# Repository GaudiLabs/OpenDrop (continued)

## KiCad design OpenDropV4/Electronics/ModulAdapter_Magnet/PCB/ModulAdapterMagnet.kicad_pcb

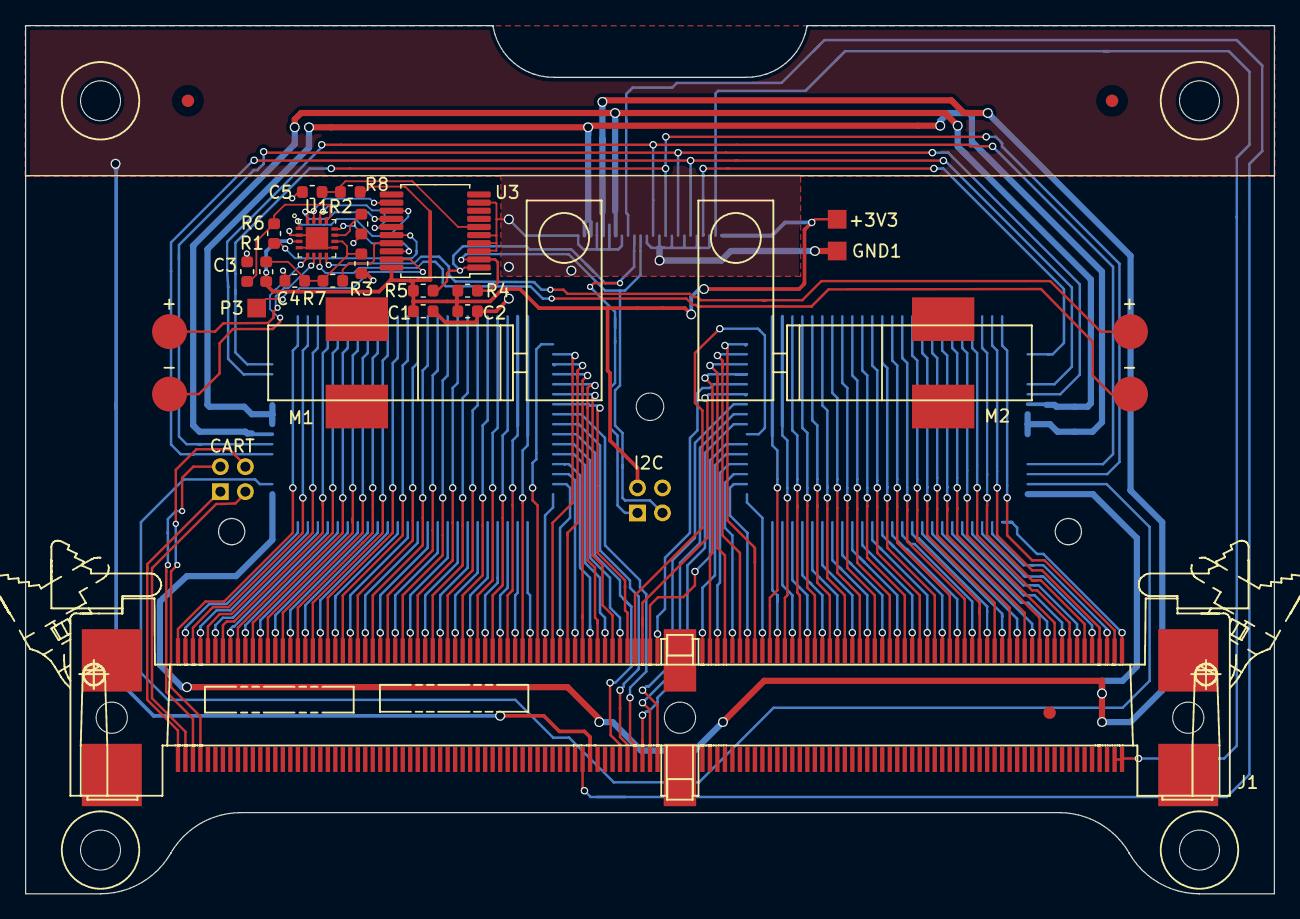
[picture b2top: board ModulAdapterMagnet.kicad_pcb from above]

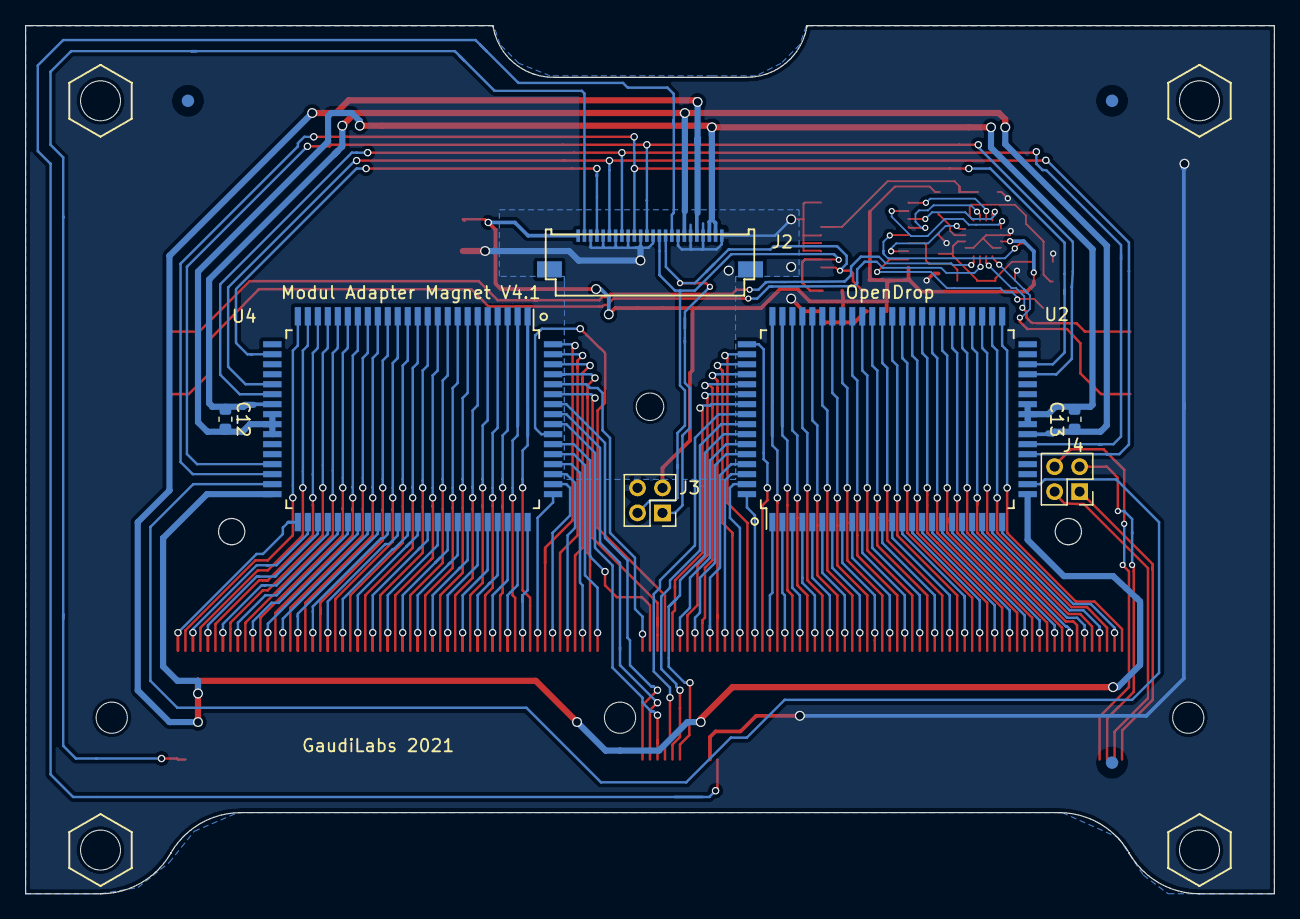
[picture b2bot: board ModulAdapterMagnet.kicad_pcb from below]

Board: 2 copper layers, 100.0 x 69.5 mm, 38 parts (10 on the bottom side), 163 nets.

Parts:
+3V3: ScrewPad2; Measurement_Point_Square-SMD-Pad_Small
C1, C4, C12, C13: 100nF; C_0603_1608Metric
C2: 10uF; C_0603_1608Metric
C3, C5: 22nF; C_0603_1608Metric
GND1: ScrewPad2; Measurement_Point_Square-SMD-Pad_Small
J1: Mini_Dimm_244; MiniDimm_06_244_200
J2: Conn_01x24_Female; FFC_MOLEX_EASYON_05mm_24
J3, J4: Conn_02x02_Top_Bottom; PinHeader_2x02_P2.00mm_Vertical
M1: Motor_DC; GreaMotor6mm_Magnet_l
M2: Motor_DC; GreaMotor6mm_Magnet
P3: ScrewPad2; Measurement_Point_Square-SMD-Pad_Small
P13, P17: ScrewPad1; MountingHoleM3
P14, P15: ScrewPad2; MountingHoleM3
R1: 100k; R_0603_1608Metric
R2: 47k; R_0603_1608Metric
R3, R7: 4.7k; R_0603_1608Metric
R4, R5, R6, R8: 10k; R_0603_1608Metric
U1: TC78H660FTG; P-VQFN16-0303-0.50-001
U2, U4: HV507; PQFP-80_14x20mm_Pitch0.8mm
U3: MCP23008_SS; SSOP-20_5.3x7.2mm_P0.65mm
X1, X2, X3, X4, X5, X6: PAD; Fiducial_1mm_Dia_2.54mm_Outer_CopperBottom

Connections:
+3V3: +3V3.1, C1.1, C2.1, J2.1, J3.3, R1.1, R4.1, R5.1, R8.1, U1.3, U3.20
BL_C: J2.6, U2.29, U4.29
BOOST: R7.2, U3.17
CLK_C: J2.12, U2.37, U4.37
DIG0: J2.15, J3.1, R5.2, U3.1
DIG1: J2.14, J3.2, R4.2, U3.2
DI_C: J2.4, U4.26
ENABLE_A: U1.15, U3.12
ENABLE_B: U1.16, U3.14
GND: C1.2, C2.2, C3.2, C4.2, C5.2, GND1.1, J1.56, J2.3, J2.5, J2.7, J2.9, J2.11, J2.13, J2.17, J2.19, J2.21, J2.24, J3.4, R2.2, R3.2, U1.2, U1.4, U1.9, U1.17, U3.3, U3.4, U3.5, U3.9
GND_C: C12.2, C13.2, J2.22, J2.23, U2.32, U2.33, U2.34, U4.32, U4.33, U4.34
J1: J1.1, J4.1
J2: J1.2, J4.2
J3: J1.3, J4.3
J4: J1.4, J4.4
LE_C: J2.10, U2.38, U4.38
MODE: R6.2, U3.16
unnamed: C3.1, R6.1, U1.13
unnamed: C4.1, R1.2, R3.1, R7.1, U1.10
unnamed: C5.1, R8.2, U3.6
unnamed: J1.60, U2.74
unnamed: J1.61, U2.73
unnamed: J1.62, U2.72
unnamed: J1.63, U4.72
unnamed: J1.64, U4.73
unnamed: J1.65, U4.74
unnamed: J1.123, U2.41
unnamed: J1.124, U2.24
unnamed: J1.125, U2.42
unnamed: J1.126, U2.23
unnamed: J1.127, U2.43
unnamed: J1.128, U2.22
unnamed: J1.129, U2.44
unnamed: J1.130, U2.21
unnamed: J1.131, U2.45
unnamed: J1.132, U2.20
unnamed: J1.133, U2.46
unnamed: J1.134, U2.19
unnamed: J1.135, U2.47
unnamed: J1.136, U2.18
unnamed: J1.137, U2.48
unnamed: J1.138, U2.17
unnamed: J1.139, U2.49
unnamed: J1.140, U2.16
unnamed: J1.141, U2.50
unnamed: J1.142, U2.15
unnamed: J1.143, U2.51
unnamed: J1.144, U2.14
unnamed: J1.145, U2.52
unnamed: J1.146, U2.13
unnamed: J1.147, U2.53
unnamed: J1.148, U2.12
unnamed: J1.149, U2.54
unnamed: J1.150, U2.11
unnamed: J1.151, U2.55
unnamed: J1.152, U2.10
unnamed: J1.153, U2.56
unnamed: J1.154, U2.9
unnamed: J1.155, U2.57
unnamed: J1.156, U2.8
unnamed: J1.157, U2.58
unnamed: J1.158, U2.7
unnamed: J1.159, U2.59
unnamed: J1.160, U2.6
unnamed: J1.161, U2.60
unnamed: J1.162, U2.5
unnamed: J1.163, U2.61
unnamed: J1.164, U2.4
unnamed: J1.165, U2.62
unnamed: J1.166, U2.3
unnamed: J1.167, U2.63
unnamed: J1.168, U2.2
unnamed: J1.169, U2.64
unnamed: J1.170, U2.1
unnamed: J1.171, U2.65
unnamed: J1.172, U2.80
unnamed: J1.173, U2.66
unnamed: J1.174, U2.79
unnamed: J1.175, U2.67
unnamed: J1.176, U2.78
unnamed: J1.177, U2.68
unnamed: J1.178, U2.77
unnamed: J1.179, U2.69
unnamed: J1.180, U2.76
unnamed: J1.181, U2.70
unnamed: J1.182, U2.75
unnamed: J1.183, U2.71
unnamed: J1.184, U4.71
unnamed: J1.185, U4.75
unnamed: J1.186, U4.70
unnamed: J1.187, U4.76
unnamed: J1.188, U4.69
unnamed: J1.189, U4.77
unnamed: J1.190, U4.68
unnamed: J1.191, U4.78
unnamed: J1.192, U4.67
unnamed: J1.193, U4.79
unnamed: J1.194, U4.66
unnamed: J1.195, U4.80
unnamed: J1.196, U4.65
unnamed: J1.197, U4.1
unnamed: J1.198, U4.64
unnamed: J1.199, U4.2
unnamed: J1.200, U4.63
unnamed: J1.201, U4.3
unnamed: J1.202, U4.62
unnamed: J1.203, U4.4
unnamed: J1.204, U4.61
unnamed: J1.205, U4.5
unnamed: J1.206, U4.60
unnamed: J1.207, U4.6
unnamed: J1.208, U4.59
unnamed: J1.209, U4.7
unnamed: J1.210, U4.58
unnamed: J1.211, U4.8
unnamed: J1.212, U4.57
unnamed: J1.213, U4.9
unnamed: J1.214, U4.56
unnamed: J1.215, U4.10
unnamed: J1.216, U4.55
unnamed: J1.217, U4.11
unnamed: J1.218, U4.54
unnamed: J1.219, U4.12
unnamed: J1.220, U4.53
unnamed: J1.221, U4.13
unnamed: J1.222, U4.52
unnamed: J1.223, U4.14
unnamed: J1.224, U4.51
unnamed: J1.225, U4.15
unnamed: J1.226, U4.50
unnamed: J1.227, U4.16
unnamed: J1.228, U4.49
unnamed: J1.229, U4.17
unnamed: J1.230, U4.48
unnamed: J1.231, U4.18
unnamed: J1.232, U4.47
unnamed: J1.233, U4.19
unnamed: J1.234, U4.46
unnamed: J1.235, U4.20
unnamed: J1.236, U4.45
unnamed: J1.237, U4.21
unnamed: J1.238, U4.44
unnamed: J1.239, U4.22
unnamed: J1.240, U4.43
unnamed: J1.241, U4.23
unnamed: J1.242, U4.42
unnamed: J1.243, U4.24
unnamed: J1.244, U4.41
unnamed: M1.1, U1.5
unnamed: M1.2, U1.6
unnamed: M2.1, U1.8
unnamed: M2.2, U1.7
unnamed: P3.1, U3.19
unnamed: R2.1, U1.11
unnamed: U2.26, U4.39
PHASE_A: U1.1, U3.13
PHASE_B: U1.14, U3.15
POL_C: J2.8, U2.30, U4.30
SENS_PAD: J1.55, J2.16
STBY: U1.12, U3.18
VDD_C: C12.1, C13.1, J2.18, U2.31, U4.31
V_GND: J1.121, J1.122, J2.2
V_HV_C: J2.20, U2.25, U4.40

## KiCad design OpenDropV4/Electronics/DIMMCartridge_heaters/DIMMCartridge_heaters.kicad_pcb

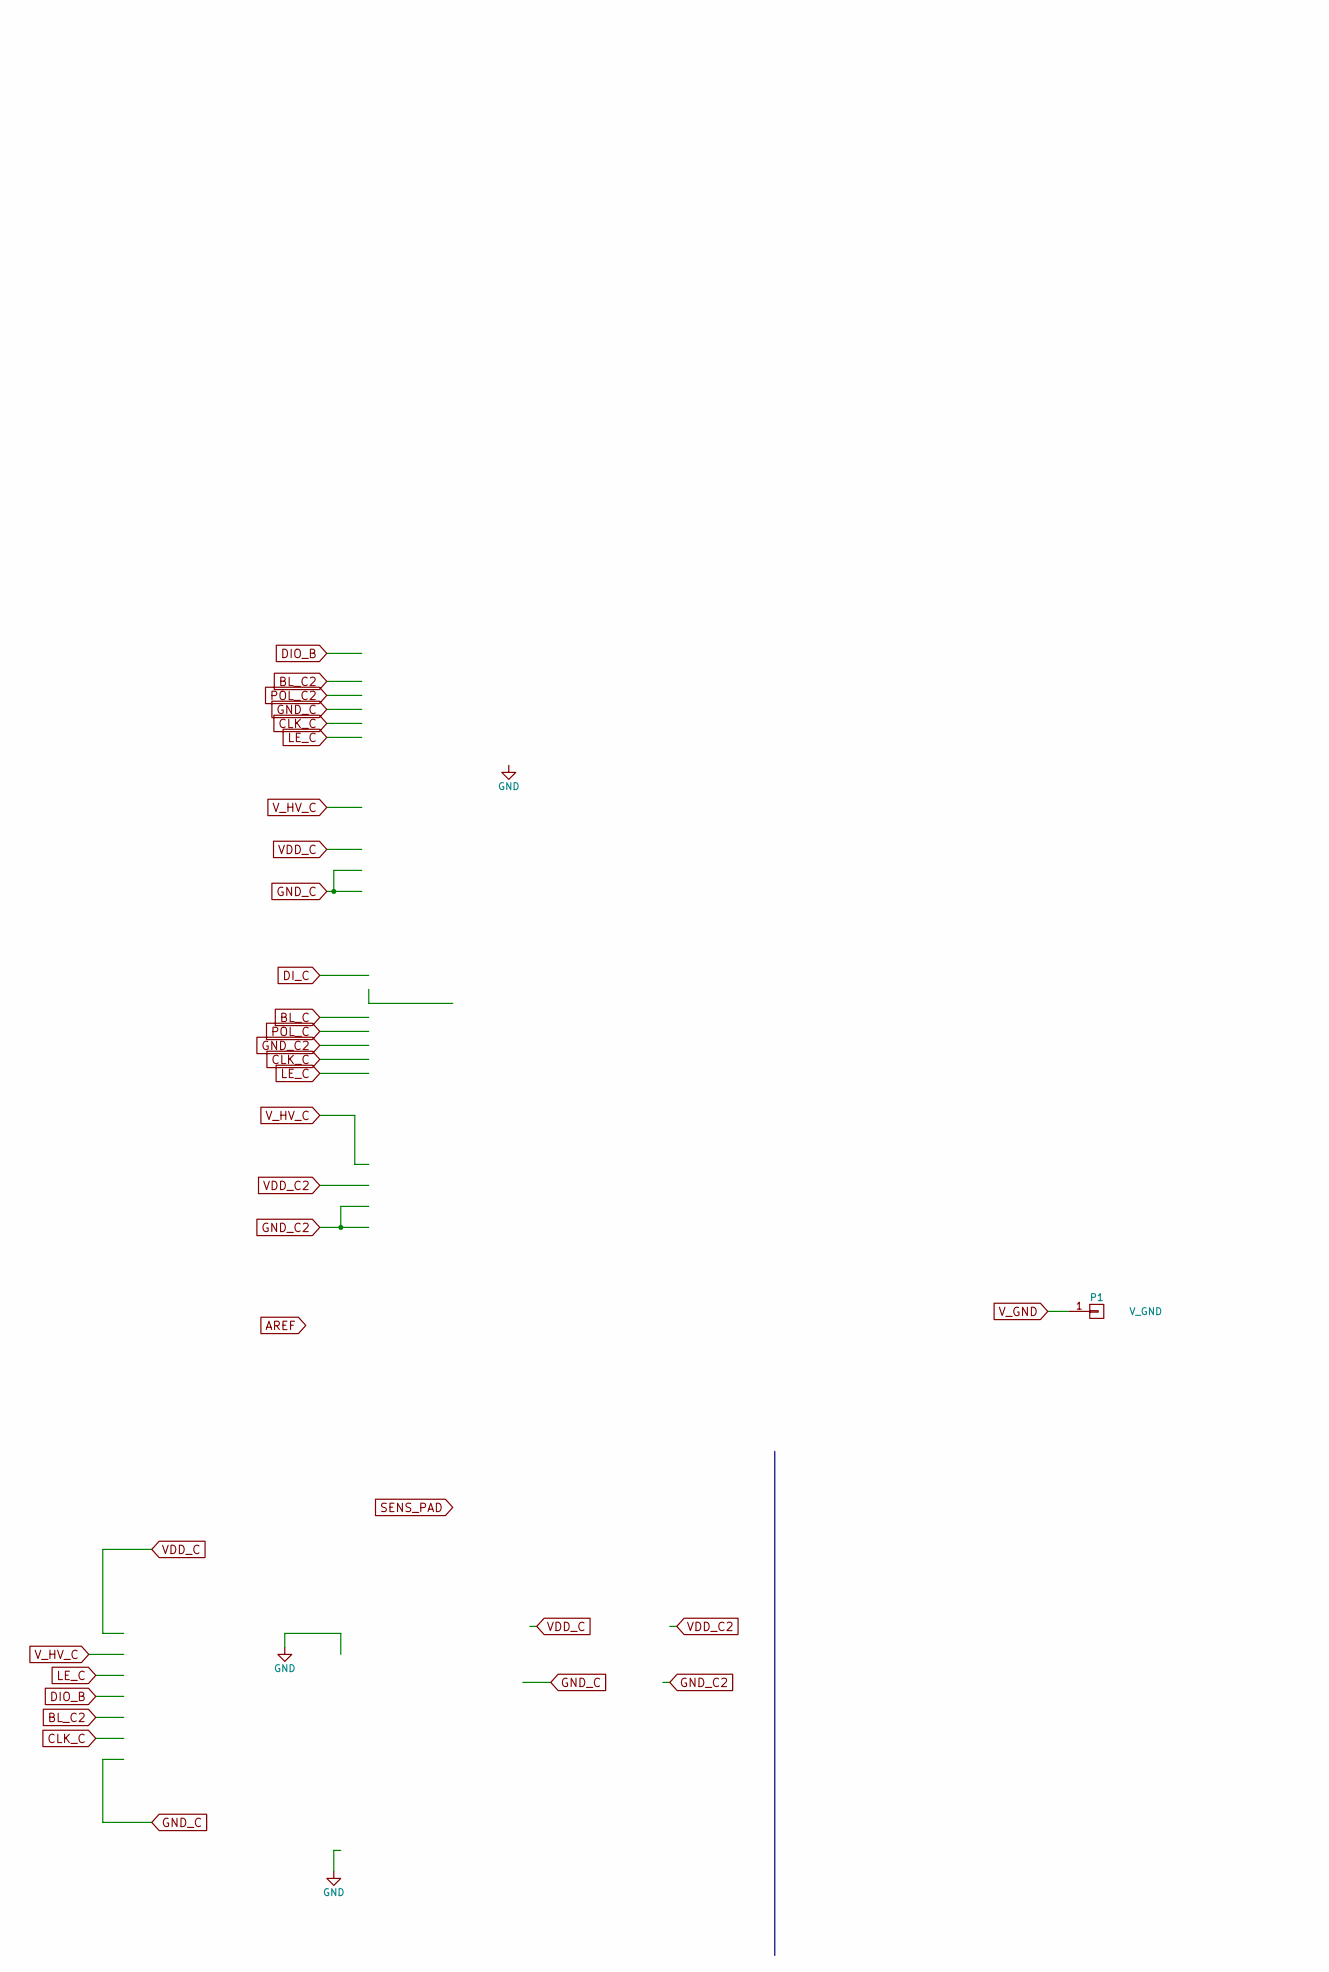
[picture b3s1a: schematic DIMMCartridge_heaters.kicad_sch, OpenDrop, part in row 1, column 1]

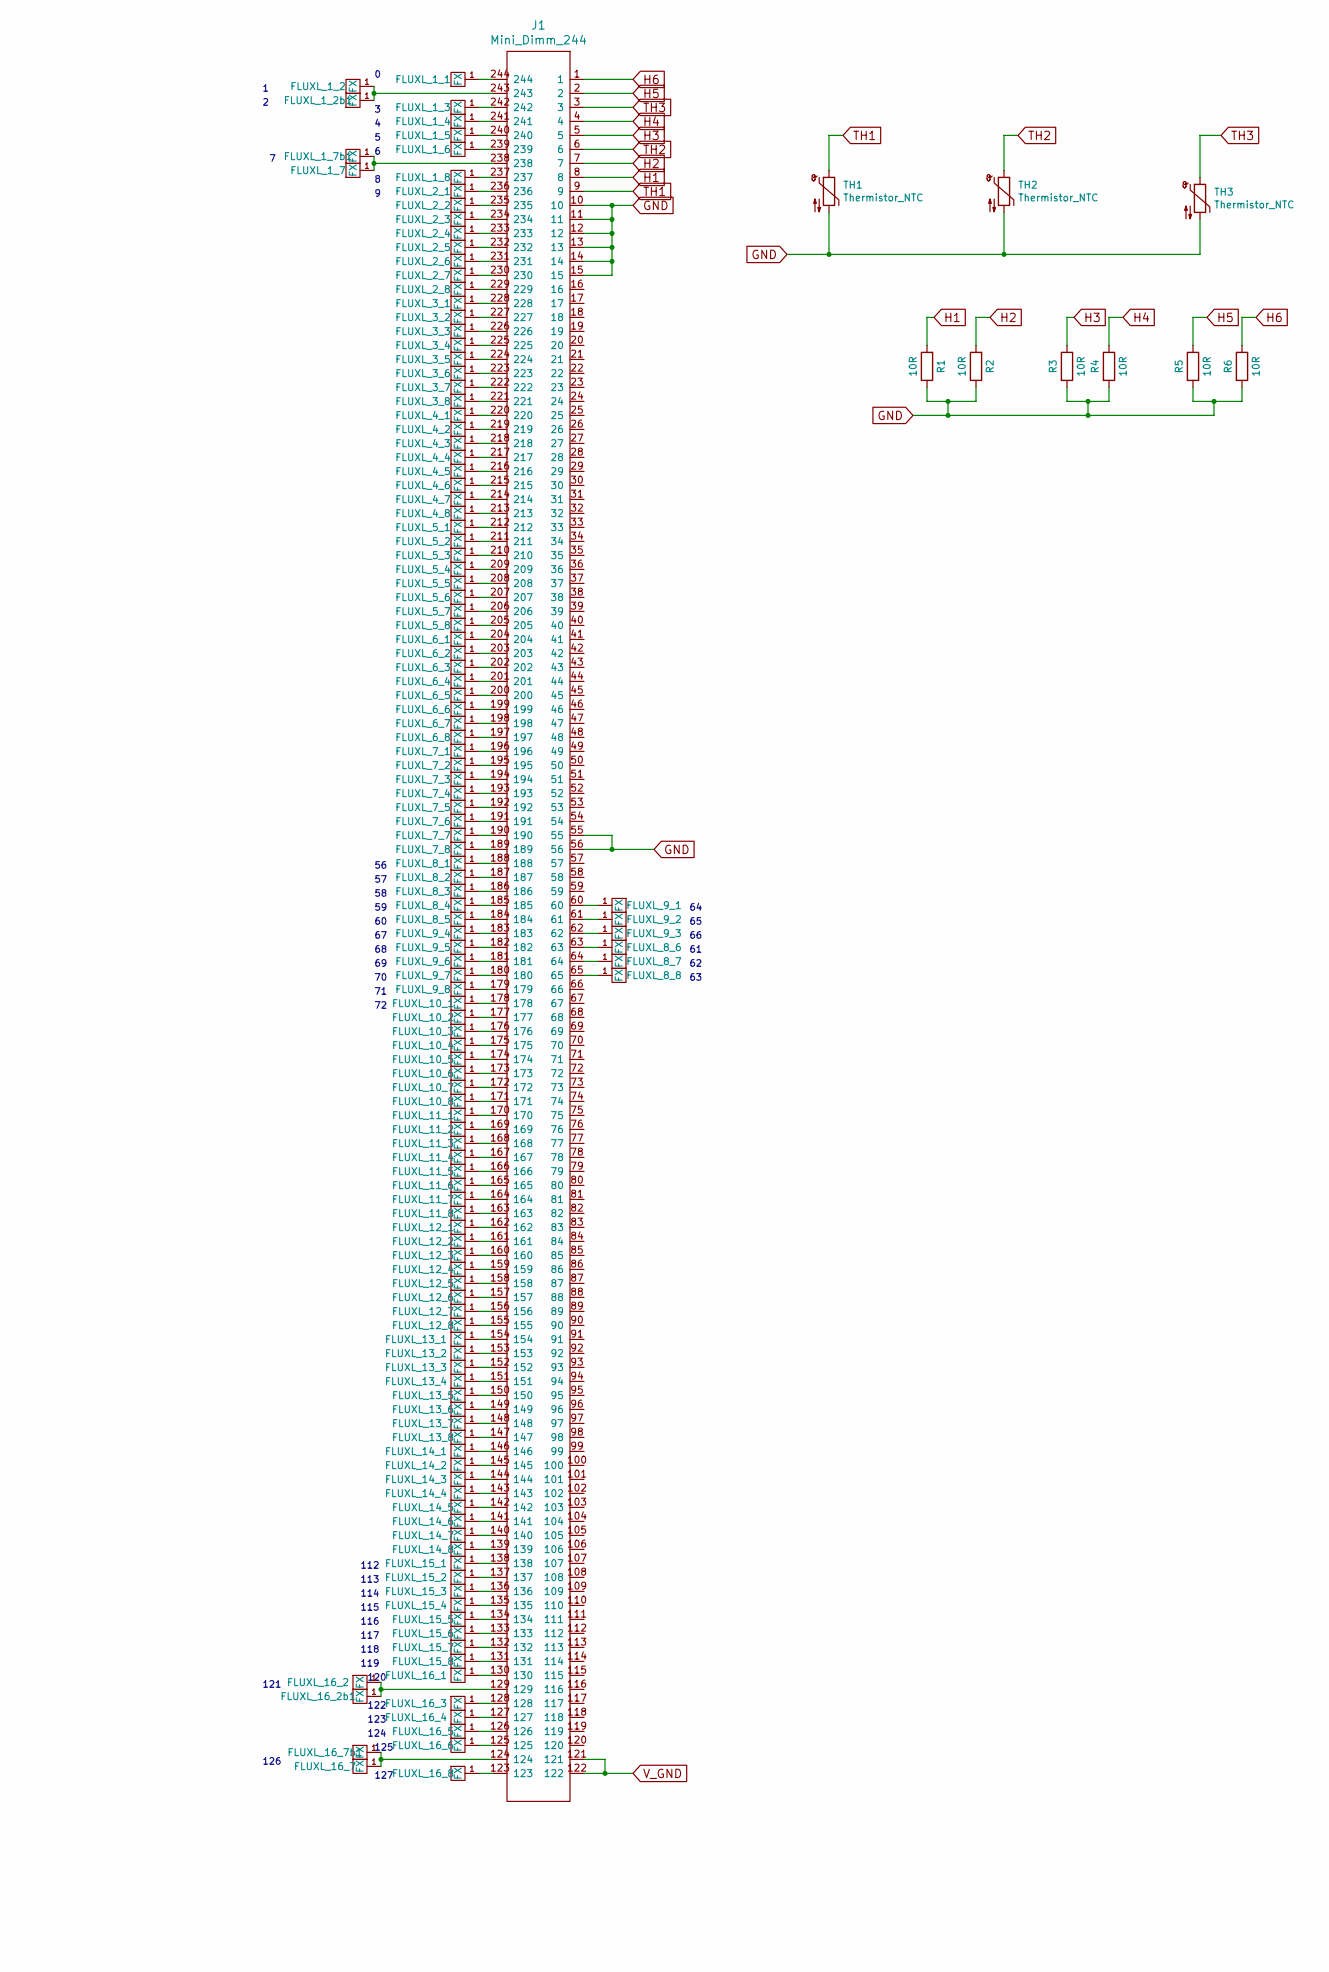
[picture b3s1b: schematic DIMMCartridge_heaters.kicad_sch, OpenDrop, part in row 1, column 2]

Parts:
FLUXL_1_1, FLUXL_1_8, FLUXL_16_1, FLUXL_16_8: FX; FLUXPAD_2_75_4MIL_4_5_res1
FLUXL_1_2, FLUXL_1_7, FLUXL_16_2, FLUXL_16_7: FX; FLUXPAD_2_75_4MIL_4_5_res4
FLUXL_1_2b1, FLUXL_1_7b1, FLUXL_16_2b1, FLUXL_16_7b1: FX; FLUXPAD_2_75_4MIL_4_5_res5
FLUXL_1_3, FLUXL_1_6, FLUXL_16_3, FLUXL_16_6: FX; FLUXPAD_2_75_4MIL_4_5_res2
FLUXL_1_4, FLUXL_1_5, FLUXL_16_4, FLUXL_16_5: FX; FLUXPAD_2_75_4MIL_4_5_res3
FLUXL_2_1, FLUXL_15_8: FX; FLUXPAD_2_75_4MIL_4_5_topleft
FLUXL_2_2, FLUXL_2_7, FLUXL_3_2, FLUXL_3_3, FLUXL_3_4, FLUXL_3_5, FLUXL_3_6, FLUXL_3_7, FLUXL_4_4, FLUXL_4_5, FLUXL_4_6, FLUXL_4_7, FLUXL_5_2, FLUXL_5_3, FLUXL_5_4, FLUXL_5_5, FLUXL_5_6, FLUXL_5_7, FLUXL_6_2, FLUXL_6_3, FLUXL_6_4, FLUXL_6_5, FLUXL_6_6, FLUXL_6_7, FLUXL_7_2, FLUXL_7_3, FLUXL_7_4, FLUXL_7_5, FLUXL_7_6, FLUXL_7_7, FLUXL_8_4, FLUXL_8_5, FLUXL_8_6, FLUXL_8_7, FLUXL_9_2, FLUXL_9_3, FLUXL_9_4, FLUXL_9_5, FLUXL_9_6, FLUXL_9_7, FLUXL_10_2, FLUXL_10_3, FLUXL_10_4, FLUXL_10_5, FLUXL_10_6, FLUXL_10_7, FLUXL_11_2, FLUXL_11_3, FLUXL_11_4, FLUXL_11_5, FLUXL_11_6, FLUXL_11_7, FLUXL_12_2, FLUXL_12_3, FLUXL_12_4, FLUXL_12_5, FLUXL_12_6, FLUXL_12_7, FLUXL_13_4, FLUXL_13_5, FLUXL_13_6, FLUXL_13_7, FLUXL_14_2, FLUXL_14_3, FLUXL_14_4, FLUXL_14_5, FLUXL_14_6, FLUXL_14_7, FLUXL_15_2, FLUXL_15_7: FX; FLUXPAD_2_75_4MIL_4_6
FLUXL_2_3, FLUXL_2_4, FLUXL_2_5, FLUXL_2_6, FLUXL_15_3, FLUXL_15_4, FLUXL_15_5, FLUXL_15_6: FX; FLUXPAD_2_75_4MIL_4_5_side
FLUXL_2_8, FLUXL_15_1: FX; FLUXPAD_2_75_4MIL_4_5_topright
FLUXL_3_1, FLUXL_3_8, FLUXL_4_1, FLUXL_4_8, FLUXL_5_1, FLUXL_5_8, FLUXL_6_1, FLUXL_6_8, FLUXL_7_1, FLUXL_7_8, FLUXL_8_1, FLUXL_8_8, FLUXL_9_1, FLUXL_9_8, FLUXL_10_1, FLUXL_10_8, FLUXL_11_1, FLUXL_11_8, FLUXL_12_1, FLUXL_12_8, FLUXL_13_1, FLUXL_13_8, FLUXL_14_1, FLUXL_14_8: FX; FLUXPAD_2_75_4MIL_4_6_top
FLUXL_4_2, FLUXL_4_3, FLUXL_8_2, FLUXL_8_3, FLUXL_13_2, FLUXL_13_3: FX; FLUXPAD_2_75_4MIL_4_5_TempSens
J1: Mini_Dimm_244; Mini_Dimm_Cartridge_244_ok
P1: V_GND; Pad_4mm_10mm
R1, R2, R3, R4, R5, R6: 10R; R_1206_3216Metric_heater
TH1, TH2, TH3: Thermistor_NTC; R_0402_1005Metric_TempSens

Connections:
GND: J1.10, J1.11, J1.12, J1.13, J1.14, J1.15, J1.55, J1.56, R1.1, R2.1, R3.2, R4.2, R5.2, R6.2, TH1.2, TH2.2, TH3.2
H1: J1.8, R1.2
H2: J1.7, R2.2
H3: J1.5, R3.1
H4: J1.4, R4.1
H5: J1.2, R5.1
H6: J1.1, R6.1
unnamed: FLUXL_1_1.1, J1.244
unnamed: FLUXL_1_2.1, FLUXL_1_2b1.1, J1.243
unnamed: FLUXL_1_3.1, J1.242
unnamed: FLUXL_1_4.1, J1.241
unnamed: FLUXL_1_5.1, J1.240
unnamed: FLUXL_1_6.1, J1.239
unnamed: FLUXL_1_7.1, FLUXL_1_7b1.1, J1.238
unnamed: FLUXL_1_8.1, J1.237
unnamed: FLUXL_2_1.1, J1.236
unnamed: FLUXL_2_2.1, J1.235
unnamed: FLUXL_2_3.1, J1.234
unnamed: FLUXL_2_4.1, J1.233
unnamed: FLUXL_2_5.1, J1.232
unnamed: FLUXL_2_6.1, J1.231
unnamed: FLUXL_2_7.1, J1.230
unnamed: FLUXL_2_8.1, J1.229
unnamed: FLUXL_3_1.1, J1.228
unnamed: FLUXL_3_2.1, J1.227
unnamed: FLUXL_3_3.1, J1.226
unnamed: FLUXL_3_4.1, J1.225
unnamed: FLUXL_3_5.1, J1.224
unnamed: FLUXL_3_6.1, J1.223
unnamed: FLUXL_3_7.1, J1.222
unnamed: FLUXL_3_8.1, J1.221
unnamed: FLUXL_4_1.1, J1.220
unnamed: FLUXL_4_2.1, J1.219
unnamed: FLUXL_4_3.1, J1.218
unnamed: FLUXL_4_4.1, J1.217
unnamed: FLUXL_4_5.1, J1.216
unnamed: FLUXL_4_6.1, J1.215
unnamed: FLUXL_4_7.1, J1.214
unnamed: FLUXL_4_8.1, J1.213
unnamed: FLUXL_5_1.1, J1.212
unnamed: FLUXL_5_2.1, J1.211
unnamed: FLUXL_5_3.1, J1.210
unnamed: FLUXL_5_4.1, J1.209
unnamed: FLUXL_5_5.1, J1.208
unnamed: FLUXL_5_6.1, J1.207
unnamed: FLUXL_5_7.1, J1.206
unnamed: FLUXL_5_8.1, J1.205
unnamed: FLUXL_6_1.1, J1.204
unnamed: FLUXL_6_2.1, J1.203
unnamed: FLUXL_6_3.1, J1.202
unnamed: FLUXL_6_4.1, J1.201
unnamed: FLUXL_6_5.1, J1.200
unnamed: FLUXL_6_6.1, J1.199
unnamed: FLUXL_6_7.1, J1.198
unnamed: FLUXL_6_8.1, J1.197
unnamed: FLUXL_7_1.1, J1.196
unnamed: FLUXL_7_2.1, J1.195
unnamed: FLUXL_7_3.1, J1.194
unnamed: FLUXL_7_4.1, J1.193
unnamed: FLUXL_7_5.1, J1.192
unnamed: FLUXL_7_6.1, J1.191
unnamed: FLUXL_7_7.1, J1.190
unnamed: FLUXL_7_8.1, J1.189
unnamed: FLUXL_8_1.1, J1.188
unnamed: FLUXL_8_2.1, J1.187
unnamed: FLUXL_8_3.1, J1.186
unnamed: FLUXL_8_4.1, J1.185
unnamed: FLUXL_8_5.1, J1.184
unnamed: FLUXL_8_6.1, J1.63
unnamed: FLUXL_8_7.1, J1.64
unnamed: FLUXL_8_8.1, J1.65
unnamed: FLUXL_9_1.1, J1.60
unnamed: FLUXL_9_2.1, J1.61
unnamed: FLUXL_9_3.1, J1.62
unnamed: FLUXL_9_4.1, J1.183
unnamed: FLUXL_9_5.1, J1.182
unnamed: FLUXL_9_6.1, J1.181
unnamed: FLUXL_9_7.1, J1.180
unnamed: FLUXL_9_8.1, J1.179
unnamed: FLUXL_10_1.1, J1.178
unnamed: FLUXL_10_2.1, J1.177
unnamed: FLUXL_10_3.1, J1.176
unnamed: FLUXL_10_4.1, J1.175
unnamed: FLUXL_10_5.1, J1.174
unnamed: FLUXL_10_6.1, J1.173
unnamed: FLUXL_10_7.1, J1.172
unnamed: FLUXL_10_8.1, J1.171
unnamed: FLUXL_11_1.1, J1.170
unnamed: FLUXL_11_2.1, J1.169
unnamed: FLUXL_11_3.1, J1.168
unnamed: FLUXL_11_4.1, J1.167
unnamed: FLUXL_11_5.1, J1.166
unnamed: FLUXL_11_6.1, J1.165
unnamed: FLUXL_11_7.1, J1.164
unnamed: FLUXL_11_8.1, J1.163
unnamed: FLUXL_12_1.1, J1.162
unnamed: FLUXL_12_2.1, J1.161
unnamed: FLUXL_12_3.1, J1.160
unnamed: FLUXL_12_4.1, J1.159
unnamed: FLUXL_12_5.1, J1.158
unnamed: FLUXL_12_6.1, J1.157
unnamed: FLUXL_12_7.1, J1.156
unnamed: FLUXL_12_8.1, J1.155
unnamed: FLUXL_13_1.1, J1.154
unnamed: FLUXL_13_2.1, J1.153
unnamed: FLUXL_13_3.1, J1.152
unnamed: FLUXL_13_4.1, J1.151
unnamed: FLUXL_13_5.1, J1.150
unnamed: FLUXL_13_6.1, J1.149
unnamed: FLUXL_13_7.1, J1.148
unnamed: FLUXL_13_8.1, J1.147
unnamed: FLUXL_14_1.1, J1.146
unnamed: FLUXL_14_2.1, J1.145
unnamed: FLUXL_14_3.1, J1.144
unnamed: FLUXL_14_4.1, J1.143
unnamed: FLUXL_14_5.1, J1.142
unnamed: FLUXL_14_6.1, J1.141
unnamed: FLUXL_14_7.1, J1.140
unnamed: FLUXL_14_8.1, J1.139
unnamed: FLUXL_15_1.1, J1.138
unnamed: FLUXL_15_2.1, J1.137
unnamed: FLUXL_15_3.1, J1.136
unnamed: FLUXL_15_4.1, J1.135
unnamed: FLUXL_15_5.1, J1.134
unnamed: FLUXL_15_6.1, J1.133
unnamed: FLUXL_15_7.1, J1.132
unnamed: FLUXL_15_8.1, J1.131
unnamed: FLUXL_16_1.1, J1.130
unnamed: FLUXL_16_2.1, FLUXL_16_2b1.1, J1.129
unnamed: FLUXL_16_3.1, J1.128
unnamed: FLUXL_16_4.1, J1.127
unnamed: FLUXL_16_5.1, J1.126
unnamed: FLUXL_16_6.1, J1.125
unnamed: FLUXL_16_7.1, FLUXL_16_7b1.1, J1.124
unnamed: FLUXL_16_8.1, J1.123
TH1: J1.9, TH1.1
TH2: J1.6, TH2.1
TH3: J1.3, TH3.1
V_GND: J1.121, J1.122, P1.1

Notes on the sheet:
120
122
118
117
121
126
124
115
123
127
114
116
112
119
113
125

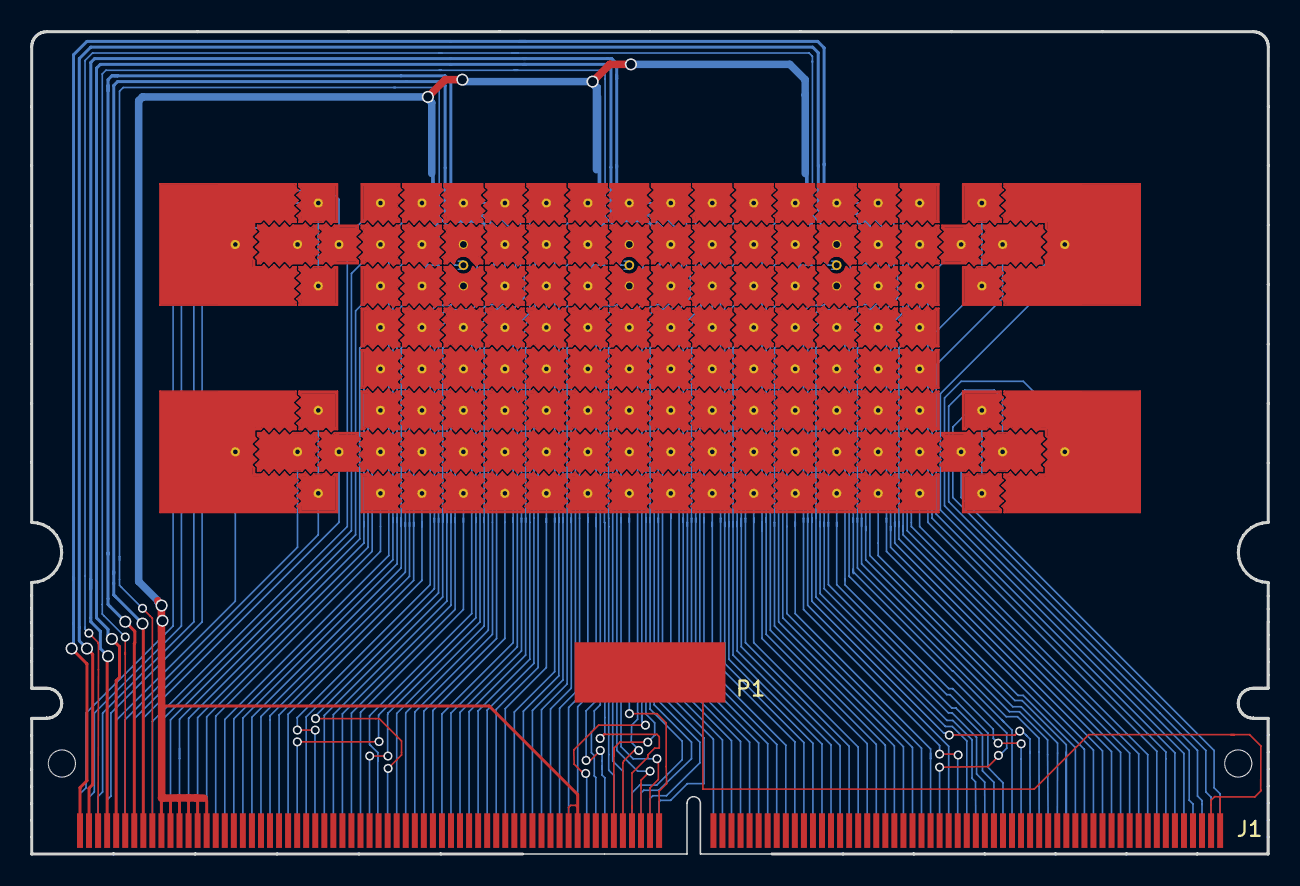
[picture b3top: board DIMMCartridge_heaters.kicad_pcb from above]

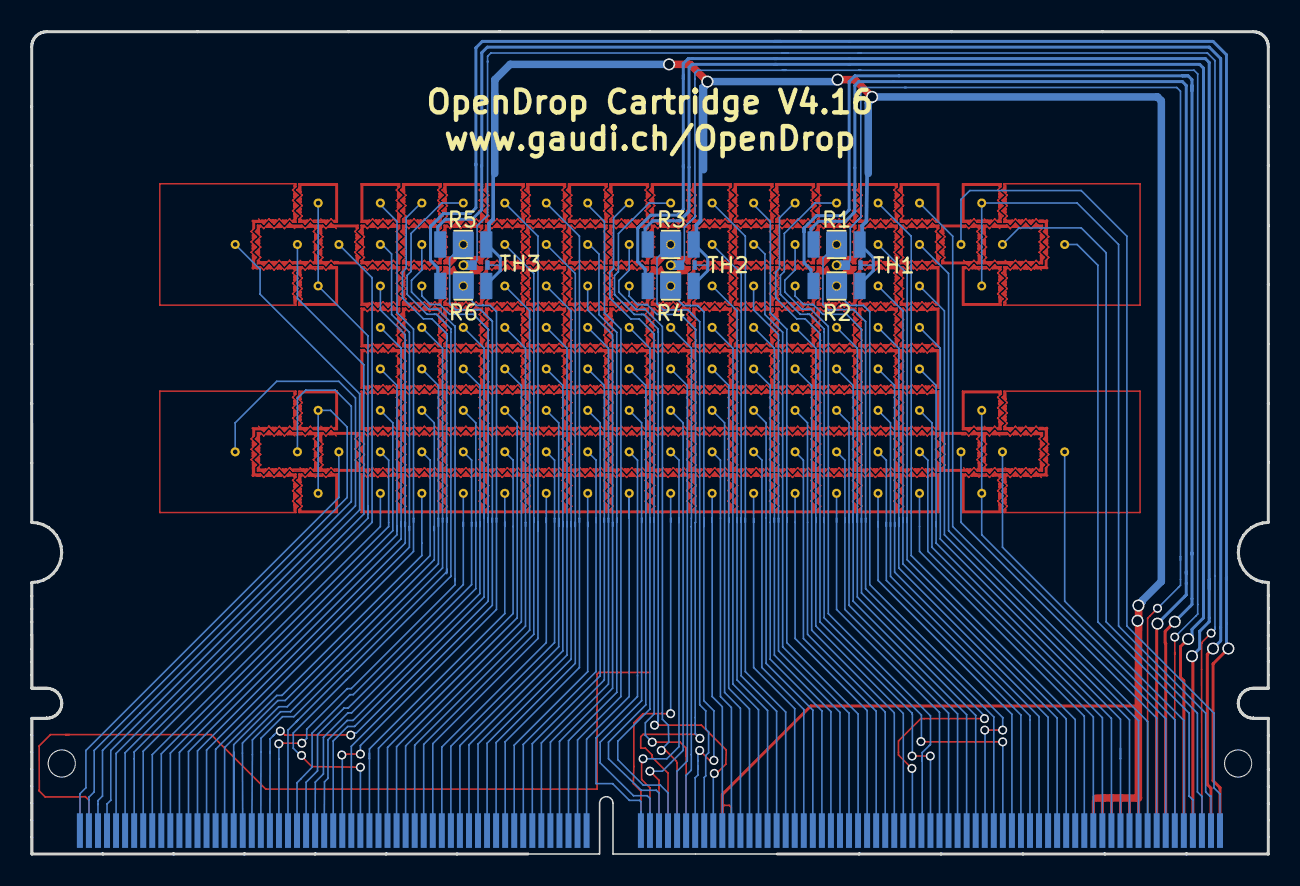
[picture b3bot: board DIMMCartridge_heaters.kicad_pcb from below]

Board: 2 copper layers, 82.0 x 54.5 mm, 143 parts (9 on the bottom side), 139 nets.

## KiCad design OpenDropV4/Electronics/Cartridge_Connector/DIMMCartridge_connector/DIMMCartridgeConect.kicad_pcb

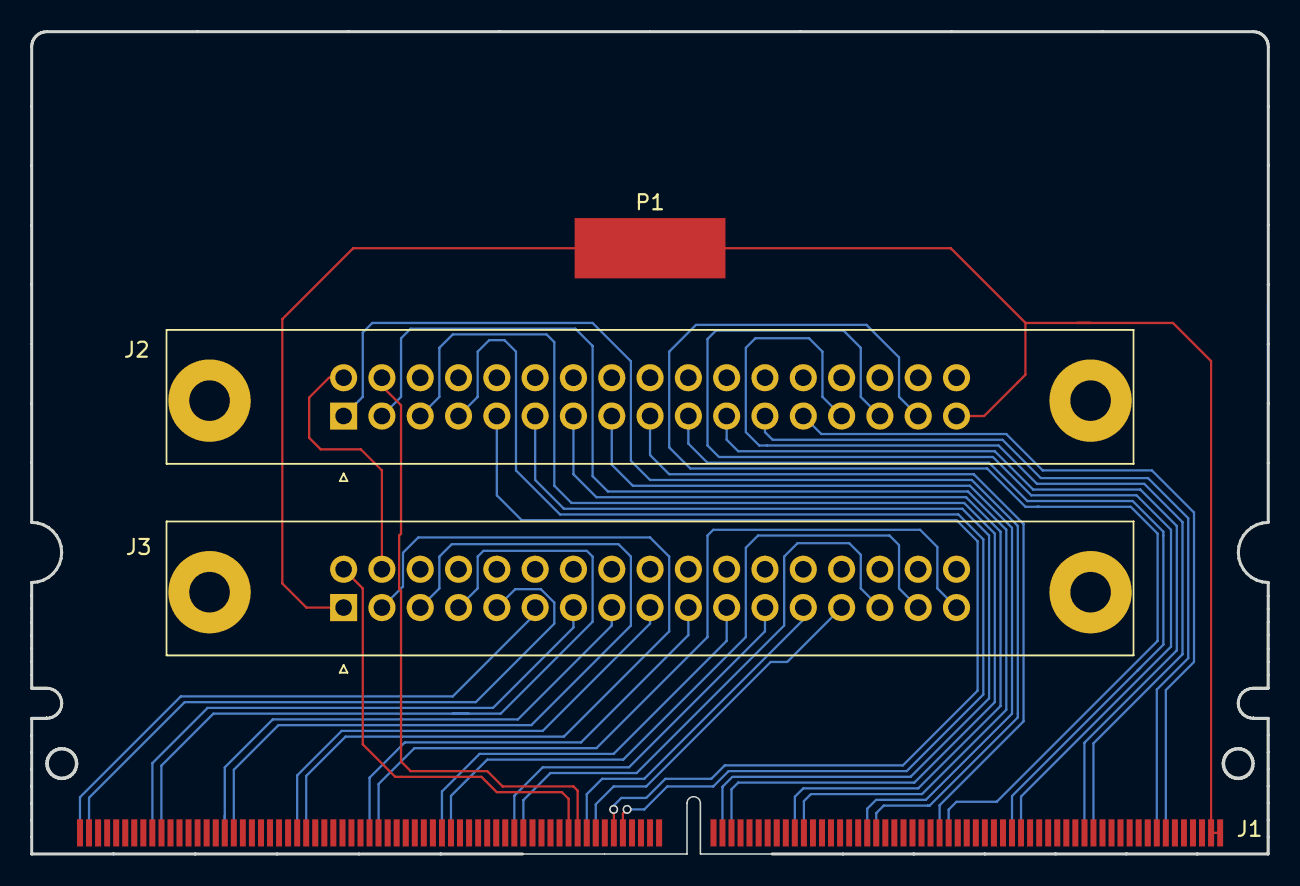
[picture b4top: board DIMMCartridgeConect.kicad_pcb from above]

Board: 2 copper layers, 82.0 x 54.5 mm, 4 parts (0 on the bottom side), 36 nets.

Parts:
J1: Mini_Dimm_244; Mini_Dimm_Cartridge_06_244
J2, J3: Conn_02x17_Odd_Even; IDC-Header_2x17_P2.54mm_Vertical_Lock
P1: V_GND; Pad_4mm_10mm

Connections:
1_1: J1.244, J3.11
1_2: J1.243, J3.9
2_1: J1.236, J3.13
2_2: J1.235, J3.7
3_1: J1.228, J3.15
3_2: J1.227, J3.5
4_1: J1.220, J3.17
4_2: J1.219, J3.3
5_1: J1.212, J3.19
5_2: J1.211, J3.33
6_1: J1.204, J3.21
6_2: J1.203, J3.31
7_1: J1.196, J3.23
7_2: J1.195, J3.29
8_1: J1.188, J3.25
8_2: J1.187, J3.27
9_1: J1.60, J2.9
9_2: J1.61, J2.7
10_1: J1.178, J2.11
10_2: J1.177, J2.5
11_1: J1.170, J2.13
11_2: J1.169, J2.3
12_1: J1.162, J2.15
12_2: J1.161, J2.1
13_1: J1.154, J2.17
13_2: J1.153, J2.31
14_1: J1.146, J2.19
14_2: J1.145, J2.29
15_1: J1.138, J2.21
15_2: J1.137, J2.27
16_1: J1.130, J2.23
16_2: J1.129, J2.25
DETECT1: J1.55, J3.2
DETECT2: J1.56, J2.4
unnamed: J2.2, J3.4
V_GND: J1.121, J1.122, J2.33, J3.1, P1.1
